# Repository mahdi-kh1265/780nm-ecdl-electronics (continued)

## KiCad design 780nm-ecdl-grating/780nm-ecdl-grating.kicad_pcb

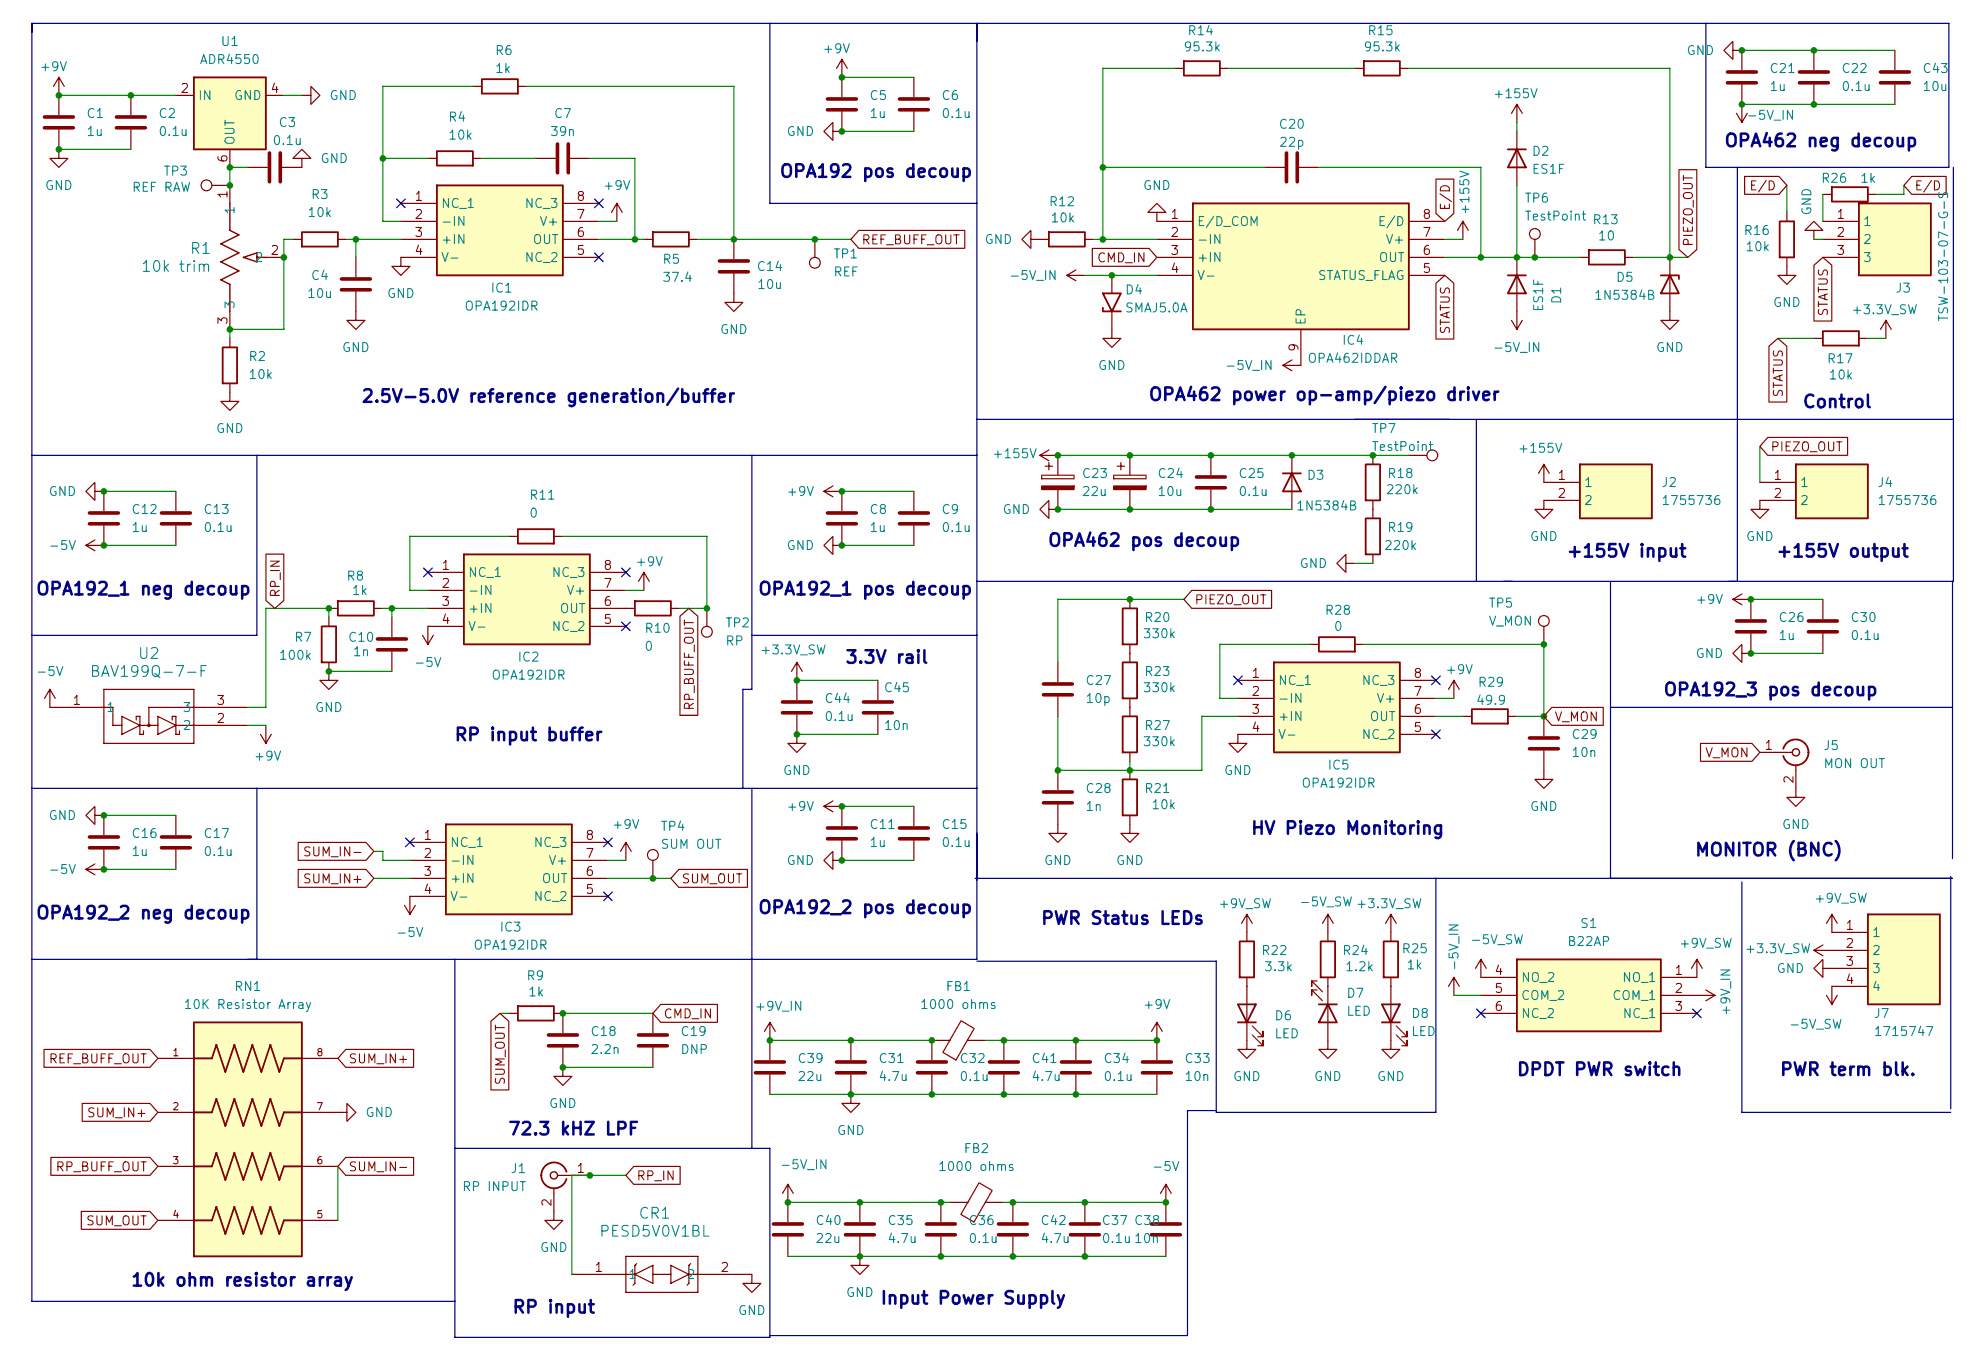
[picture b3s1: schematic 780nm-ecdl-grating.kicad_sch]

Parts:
C1, C5, C8, C11, C12, C16, C21, C26: 1u; C_0603_1608Metric
C2, C3, C6, C9, C13, C15, C17, C22, C30, C32, C34, C36, C37, C44: 0.1u; C_0603_1608Metric
C4, C14: 10u; C_0805_2012Metric
C7: 39n; C_0402_1005Metric
C10: 1n; C_0402_1005Metric
C18: 2.2n; C_0402_1005Metric
C19: DNP; C_0402_1005Metric
C20: 22p; R_0603_1608Metric
C23: 22u; PCAP_10x20-THRU-ELECT_NCA
C24: 10u; CAP_PAN_10X16_PAN
C25: 0.1u; CAP_PHE426_AH_KEM
C27: 10p; C_0603_1608Metric
C28: 1n; C_1206_3216Metric
C29, C33, C38, C45: 10n; C_0402_1005Metric
C31, C35, C41, C42: 4.7u; C_0603_1608Metric
C39, C40: 22u; C_0805_2012Metric
C43: 10u; C_0603_1608Metric
CR1: PESD5V0V1BL; DFN1006-2_SOD882_NEX
D1, D2: ES1F; D_SMA
D3: 1N5384B; D_SMA
D4: SMAJ5.0A; D_SMA
D5: 1N5384B; D_DO-201_P12.70mm_Horizontal
D6, D7, D8: LED; LED_0603_1608Metric
FB1, FB2: 1000 ohms; L_0603_1608Metric
IC1, IC2, IC3, IC5: OPA192IDR; SOIC127P600X175-8N; Mouser Part Number 595-OPA192IDR
IC4: OPA462IDDAR; SOIC127P600X170-9N; Mouser Part Number 595-OPA462IDDAR
J1: RP INPUT; CONN_SMA-J-P-H-ST-TH1_SAI
J2, J4: 1755736; Mouser Part Number 651-1755736
J3: TSW-103-07-G-S; TSW-103-XX-YY-S; Mouser Part Number 200-TSW10307GS
J5: MON OUT; CONN_112404_AMP
J7: 1715747; Mouser Part Number 651-1715747
R1: 10k trim; POT_3296W
R2, R3, R16, R17: 10k; R_0603_1608Metric
R4: 10k; C_0402_1005Metric
R5: 37.4; R_0603_1608Metric
R6, R8, R9, R25, R26: 1k; R_0603_1608Metric
R7: 100k; R_0603_1608Metric
R10, R11: 0; R_0402_1005Metric
R12, R21: 10k; R_1206_3216Metric
R13: 10; R_1206_3216Metric
R14, R15: 95.3k; R_1210_3225Metric
R18, R19: 220k; R_1206_3216Metric
R20, R23, R27: 330k; R_1206_3216Metric
R22: 3.3k; R_0603_1608Metric
R24: 1.2k; R_0603_1608Metric
R28: 0; R_1206_3216Metric
R29: 49.9; R_0603_1608Metric
RN1: 10K Resistor Array; RESCAXS80P320X150X55-8N; PARTREV 17-Aug-2022
S1: B22AP; Mouser Part Number 633-B22AP
TP1: REF; TestPoint_Keystone_5015_Micro_Mini
TP2: RP; TestPoint_Keystone_5015_Micro_Mini
TP3: REF RAW; TestPoint_Keystone_5015_Micro_Mini
TP4: SUM OUT; TestPoint_Keystone_5015_Micro_Mini
TP5: V_MON; TestPoint_Keystone_5015_Micro_Mini
TP6, TP7: TestPoint; TestPoint_Pad_D4.0mm
U1: ADR4550; SOIC-8_3.9x4.9mm_P1.27mm
U2: BAV199Q-7-F; SOT23_BAV_DIO

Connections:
+3.3V_SW: C44.1, C45.1, J7.2, R17.2, R25.1
+9V: C1.1, C2.1, C5.1, C6.1, C8.1, C9.1, C11.1, C15.1, C26.1, C30.1, C33.1, C34.1, C41.1, FB1.2, IC1.7 (V+), IC2.7 (V+), IC3.7 (V+), IC5.7 (V+), U1.2 (IN), U2.2
+9V_IN: C31.1, C32.1, C39.1, FB1.1, S1.2 (COM_1)
+9V_SW: J7.1, R22.1, S1.1 (NO_1)
+155V: C23.1, C24.1, C25.1, D2.1 (K), D3.1 (K), IC4.7 (V+), J2.1, R18.1, TP7.1; also elsewhere on the board
-5V: C12.2, C13.2, C16.2, C17.2, C37.1, C38.1, C42.1, FB2.2, IC2.4 (V-), IC3.4 (V-), U2.1
-5V_IN: C21.2, C22.2, C35.1, C36.1, C40.1, C43.2, D1.2 (A), D4.2 (A2), FB2.1, IC4.4 (V-), IC4.9 (EP), S1.5 (COM_2)
-5V_SW: J7.4, R24.1, S1.4 (NO_2)
CMD_IN: C18.1, C19.1, IC4.3 (+IN), R9.1; also elsewhere on the board
E/D: IC4.8 (E/D), R16.1, R26.1
GND: C1.2, C2.2, C3.2, C4.1, C5.2, C6.2, C8.2, C9.2, C10.2, C11.2, C12.1, C13.1, C14.1, C15.2, C16.1, C17.1, C18.2, C19.2, C21.1, C22.1, C23.2, C24.2, C25.2, C26.2, C28.2, C29.2, C30.2, C31.2, C32.2, C33.2, C34.2, C35.2, C36.2, C37.2, C38.2, C39.2, C40.2, C41.2, C42.2, C43.1, C44.2, C45.2, CR1.2, D3.2 (A), D4.1 (A1), D5.2 (A), D6.1 (K), D7.2 (A), D8.1 (K), IC1.4 (V-), IC4.1 (E/D_COM), IC5.4 (V-), J1.2 (Ext), J1.3, J1.4, J1.5, J2.2, J3.2, J4.2, J5.2 (Ext), J5.3, J5.4, J5.5, J7.3, R2.2, R7.2, R12.2, R16.2, R19.2, R21.2, RN1.7, U1.4 (GND)
unnamed: C7.1, R4.2
unnamed 12: C20.2, D1.1 (K), D2.2 (A), IC4.6 (OUT), R13.2, TP6.1; also elsewhere on the board
unnamed: D6.2 (A), R22.2
unnamed: D7.1 (K), R24.2
unnamed: D8.2 (A), R25.2
unnamed: C4.2, IC1.3 (+IN), R3.1
unnamed: IC1.2 (-IN), R4.1, R6.1
unnamed: C7.2, IC1.6 (OUT), R5.2
unnamed: C10.1, IC2.3 (+IN), R8.1
unnamed: IC2.2 (-IN), R11.1
unnamed: IC2.6 (OUT), R10.2
unnamed: C20.1, IC4.2 (-IN), R12.1, R14.2
unnamed: C27.2, C28.1, IC5.3 (+IN), R21.1, R27.2
unnamed: IC5.2 (-IN), R28.1
unnamed: IC5.6 (OUT), R29.1
unnamed: J3.1, R26.2
unnamed: R1.2, R1.3, R2.1, R3.2
unnamed: R14.1, R15.2
unnamed: R18.2, R19.1
unnamed: R20.2, R23.1
unnamed: R23.2, R27.1
unnamed: C3.1, R1.1, TP3.1 (1_1), U1.6 (OUT)
PIEZO_OUT: C27.1, D5.1 (K), J4.1, R13.1, R15.1, R20.1
REF_BUFF_OUT: C14.2, R5.1, R6.2, RN1.1, TP1.1 (1_1)
RP_BUFF_OUT: R10.1, R11.2, RN1.3, TP2.1 (1_1)
RP_IN: CR1.1, J1.1 (In), R7.1, R8.2, U2.3
STATUS: IC4.5 (STATUS_FLAG), J3.3, R17.1
SUM_IN+: IC3.3 (+IN), RN1.2, RN1.8
SUM_IN-: IC3.2 (-IN), RN1.5, RN1.6
SUM_OUT: IC3.6 (OUT), R9.2, RN1.4, TP4.1
V_MON: C29.1, J5.1 (In), R28.2, R29.2, TP5.1; also elsewhere on the board

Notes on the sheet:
MONITOR (BNC)
OPA192_1 neg decoup
Control
OPA462 neg decoup
PWR Status LEDs
2.5V-5.0V reference generation/buffer
10k ohm resistor array
RP input buffer
3.3V rail
RP input
72.3 kHZ LPF
Input Power Supply
+155V input
OPA462 power op-amp/piezo driver
DPDT PWR switch
OPA192_2 neg decoup
PWR term blk.
OPA192 pos decoup
OPA192_1 pos decoup
+155V output
OPA462 pos decoup
HV Piezo Monitoring
OPA192_2 pos decoup
OPA192_3 pos decoup

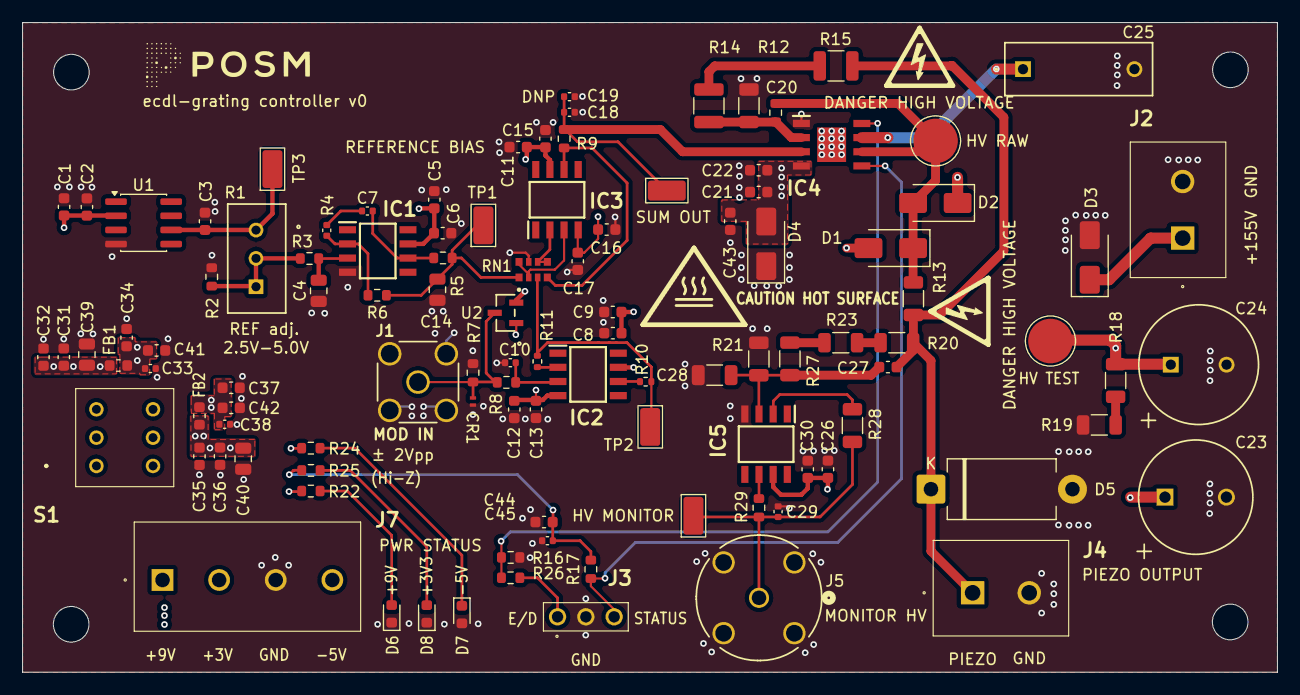
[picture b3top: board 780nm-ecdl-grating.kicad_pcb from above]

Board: 4 copper layers, 112.6 x 58.3 mm, 109 parts (0 on the bottom side), 42 nets.

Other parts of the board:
780nm-ecdl grating v0: LOGO; posm-logo-footprint
HV MONITOR: V_MON; TestPoint_Keystone_5015_Micro_Mini
HV RAW: TestPoint; TestPoint_Pad_D4.0mm
HV TEST: TestPoint; TestPoint_Pad_D4.0mm
SUM OUT: SUM OUT; TestPoint_Keystone_5015_Micro_Mini
SYM: Caution_Hot_Surface_FinalFit_12x12mm_Silk

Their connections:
+155V: HV TEST.1 (1_1); also elsewhere on the board
CMD_IN: SUM OUT.1 (1_1); also elsewhere on the board
unnamed 12: HV RAW.1 (1_1); also elsewhere on the board
V_MON: HV MONITOR.1 (1_1); also elsewhere on the board
